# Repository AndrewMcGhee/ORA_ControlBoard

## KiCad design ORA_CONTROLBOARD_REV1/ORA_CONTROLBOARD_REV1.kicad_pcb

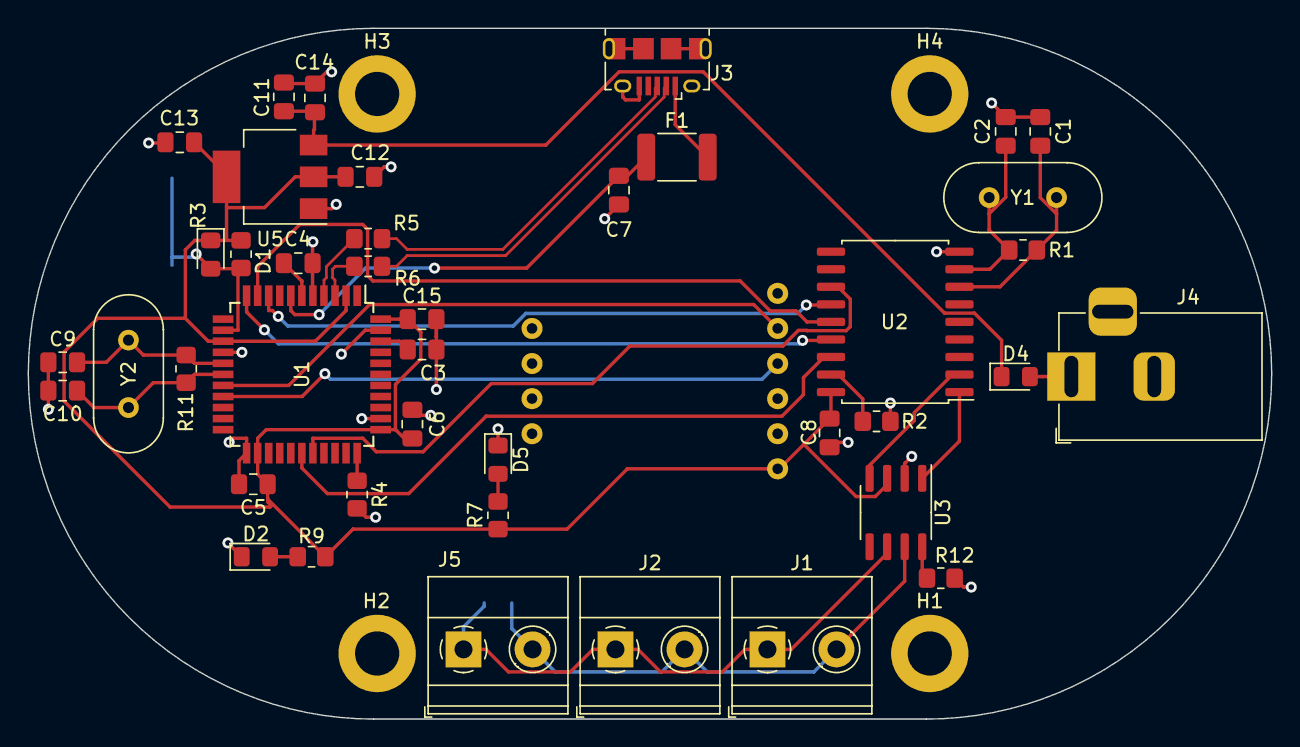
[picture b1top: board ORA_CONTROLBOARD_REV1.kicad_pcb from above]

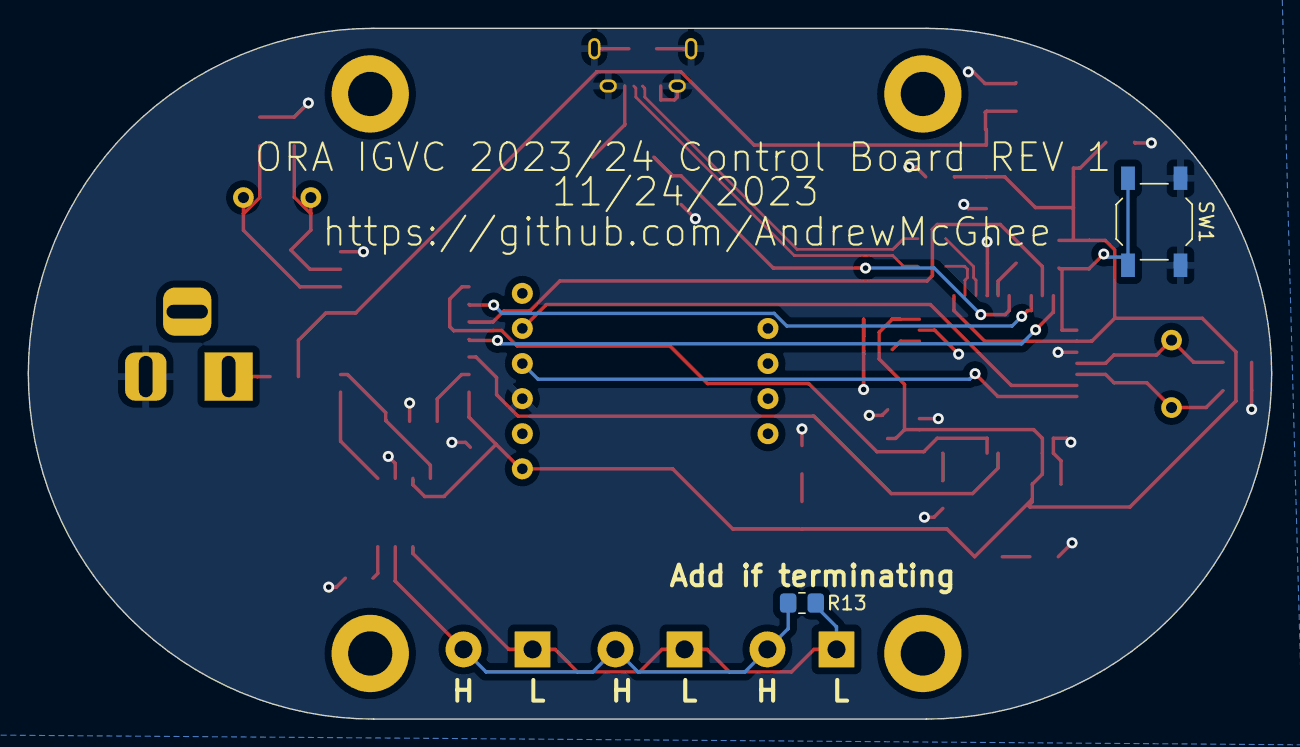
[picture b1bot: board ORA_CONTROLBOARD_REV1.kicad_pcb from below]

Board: 2 copper layers, 90.0 x 50.0 mm, 48 parts (2 on the bottom side), 33 nets.

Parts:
C1, C2, C9, C10, C13: 22uF; C_0805_2012Metric_Pad1.18x1.45mm_HandSolder
C3, C5, C6, C7, C8, C14: 100nF; C_0805_2012Metric_Pad1.18x1.45mm_HandSolder
C4, C15: 1uF; C_0805_2012Metric_Pad1.18x1.45mm_HandSolder
C11: 10nF; C_0805_2012Metric_Pad1.18x1.45mm_HandSolder
C12: 100uF; C_0805_2012Metric_Pad1.18x1.45mm_HandSolder
D1: rst; D_0805_2012Metric_Pad1.15x1.40mm_HandSolder
D2: LED_Small; LED_0805_2012Metric_Pad1.15x1.40mm_HandSolder
D4: PWRIN; D_0805_2012Metric_Pad1.15x1.40mm_HandSolder
D5: IMU_LED; LED_0805_2012Metric_Pad1.15x1.40mm_HandSolder
F1: MF-MSMF050-2; Fuse_1812_4532Metric_Pad1.30x3.40mm_HandSolder
H1, H2, H3, H4: MountingHole_Pad; MountingHole_3.2mm_M3_DIN965_Pad
J1, J2, J5: CAN; TerminalBlock_Phoenix_MKDS-1,5-2_1x02_P5.00mm_Horizontal
J3: USB_B_Micro; USB_Micro-B_Amphenol_10118194_Horizontal
J4: PW IN; BarrelJack_Horizontal
R1, R11: 1M; R_0805_2012Metric_Pad1.20x1.40mm_HandSolder
R2, R3, R4, R12: 10k; R_0805_2012Metric_Pad1.20x1.40mm_HandSolder
R5, R6: 22; R_0805_2012Metric_Pad1.20x1.40mm_HandSolder
R7, R9: 470; R_0805_2012Metric_Pad1.20x1.40mm_HandSolder
R13: 120; R_0805_2012Metric_Pad1.20x1.40mm_HandSolder
SW1: Reset; SW_SPST_TL3342
U1: ATmega32U4-A; TQFP-44_10x10mm_P0.8mm
U2: MCP2515-xSO; SOIC-18W_7.5x11.6mm_P1.27mm
U3: MCP2551-I-SN; SOIC-8_3.9x4.9mm_P1.27mm
U5: NCP1117-5.0_SOT223; SOT-223-3_TabPin2
U6: IMU_MOUNT
Y1: 8Mhz; Crystal_HC49-4H_Vertical
Y2: 16MHz; Crystal_HC49-4H_Vertical

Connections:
(USB) D+: J3.3 (D+), R5.1
(USB) D-: J3.2 (D-), R6.2
+5V: C5.1, C6.1, C8.1, C12.2, C13.1, C15.1, D1.1 (K), R3.2, R7.1, R9.1, U1.2 (UVCC), U1.14 (VCC), U1.24 (AVCC), U1.34 (VCC), U1.44 (AVCC), U2.18 (VDD), U3.3 (VDD), U5.2 (VO), U6.10 (Vin)
CAN_CS: U1.28 (PB4), U2.16 (~CS)
CAN_H: J1.2, J2.2, J5.2, R13.1, U3.7 (CANH)
CAN_INT: U1.29 (PB5), U2.12 (~INT)
CAN_L: J1.1, J2.1, J5.1, R13.2, U3.6 (CANL)
CAN_SCK: U1.9 (PB1), U2.13 (SCK)
CAN_SI: U1.10 (PB2), U2.14 (SI)
CAN_SO: U1.11 (PB3), U2.15 (SO)
D+: R5.2, U1.4 (D+)
D-: R6.1, U1.3 (D-)
GND: C1.1, C2.2, C3.1, C4.1, C5.2, C6.2, C7.2, C8.2, C9.1, C10.2, C11.1, C12.1, C13.2, C14.1, C15.2, D2.1 (K), D5.1 (K), J3.5 (GND), J3.6 (Shield), J4.2, R2.1, R4.2, R12.2, SW1.1, U1.5 (UGND), U1.15 (GND), U1.23 (GND), U1.35 (GND), U1.43 (GND), U2.9 (VSS), U3.2 (VSS), U5.1 (GND), U6.8 (GND)
IMU_SCL: U1.18 (PD0), U6.6 (SCL)
IMU_SDA: U1.19 (PD1), U6.7 (SDA)
unnamed: D2.2 (A), R9.2
unnamed: D4.2 (A), J4.1
unnamed: D5.2 (A), R7.2
unnamed: F1.2, J3.1 (VBUS)
unnamed: C3.2, U1.42 (AREF)
unnamed: C4.2, U1.6 (UCAP)
unnamed: R4.1, U1.33 (~HWB/PE2)
unnamed: C2.1, R1.2, U2.8 (OSC1), Y1.1
unnamed: C1.2, R1.1, U2.7 (OSC2), Y1.2
unnamed: U2.2 (RXCAN), U3.4 (RXD)
unnamed: U2.1 (TXCAN), U3.1 (TXD)
unnamed: R2.2, U2.17 (~RESET)
unnamed: R12.1, U3.8 (Rs)
PWRIN: C11.2, C14.2, D4.1 (K), U5.3 (VI)
RST: D1.2 (A), R3.1, SW1.2, U1.13 (~RESET)
VBUS: C7.1, F1.1, U1.7 (VBUS)
XTAL1: C10.1, R11.2, U1.17 (XTAL1), Y2.1
XTAL2: C9.2, R11.1, U1.16 (XTAL2), Y2.2

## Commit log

2023-11-23 Basis
2023-12-23 I broke it
2023-12-23 Wee wooo
